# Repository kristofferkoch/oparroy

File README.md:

# oparroy

A read+write, fault-tolerant ring communication protocol for **extremely
cheap** microcontroller nodes, inspired by the WS2812 single-wire
protocol.

Unlike WS2812's write-only daisy chain, oparroy closes the chain into a
ring so nodes can both send and receive. The physical layer is designed
so that **no single point of failure** — a broken connector (permanent
or intermittent), or a dead/hung microcontroller — partitions the ring:

- The ring is dual: every segment carries two counter-rotating data
  rings with symmetric rebroadcast, so any single fault leaves every
  node reachable ([DESIGN.md §3](DESIGN.md#3-ring-topology-and-bypass)).
- Bypass wiring routes around failed interconnects.
- Each node has a semi-passive hardware watchdog that bypasses the
  node's RX→TX path unless the MCU actively keeps the bypass disabled.
- Status LEDs make faults visually locatable to node and segment
  without instruments.

**Extremely low node cost is the central design principle** (sub-3-NOK
MCU class); every other driver — resilience, repairability,
testability — is achieved subject to it. Supervisor and test
infrastructure, by contrast, may cost freely.

## Hardware direction

- **Node MCU: CH32V003F4P6** — 48 MHz
  RV32EC in TSSOP-20, on-chip comparator routable to timer capture,
  ~$0.14 @4k. Clocked from the factory-trimmed internal HSI — no
  crystal; the ratio-metric PHY makes absolute clock accuracy
  irrelevant. Rationale:
  [docs/mcu-research.md](docs/mcu-research.md);
  extracted part facts: `datasheets/CH32V003/notes/`.
- **Supervisor: RP2040** — its PIO is the re-timing PHY engine and
  golden-reference transceiver; on the test board its PIO also runs as
  a logic analyzer on the instrumented boundary node ([DESIGN.md §6](DESIGN.md#6-test-board)).
- **PHY**: WS2812-compatible duty-coded
  PWM cells with ratio-metric decode at an 800 kbit/s anchor,
  comparator RX + DMA, per-bit cut-through re-timing, positional
  addressing, and the frame gap as a ring-wide vsync latch
  ([DESIGN.md §2](DESIGN.md#2-physical-layer); analysis:
  [docs/phy-analysis.md](docs/phy-analysis.md)).
- **Segment interconnect** ([DESIGN.md §2.1](DESIGN.md#21-ring-power-rail), [§3](DESIGN.md#3-ring-topology-and-bypass)): 2x5-pin IDC
  connectors (2.54 mm box headers on 3M 3365/10 ribbon) carry both
  counter-rotating data rings plus power — a single 3.3 V
  rail that is both the signaling rail and node power, and a raw
  5–18 V rail for payloads with their own buck. On 3M 3365 ribbon,
  segments reach **10 m unamplified**; the 470 Ω TX series resistor,
  not the cable, sets the limit (simulation:
  [docs/cable-reach.md](docs/cable-reach.md)).
- **Node I/O**: potmeter, buttons/matrix, capacitive touch, I2C
  accelerometer, LEDs, buzzer — nodes are smart peripherals serving
  cooked data (Bela/Trill pattern, see
  [docs/bela-lessons.md](docs/bela-lessons.md)).
- **Test board**: 8 ring nodes + supervisor, full fault injection
  (per-segment open/short, per-node power cut, keep-alive cut), everything
  scriptable for hands-off hardware-in-the-loop testing. Doubles as
  the **demonstrator**: some nodes carry human-facing I/O
  (potentiometer, buttons, LEDs, buzzer), each input overridable by
  the supervisor so scripted runs stay hands-off ([DESIGN.md §6](DESIGN.md#6-test-board)).
  4-layer, self-documenting silkscreen. Prototypes assembled by
  **JLCPCB Economic PCBA**; part
  selection is inventory-driven — minimize unique Extended BOM lines.

## Firmware direction

- **Freestanding C++, no standard library** — RAII, typed volatile
  structs over memory-mapped I/O, `constexpr` config; no
  exceptions/RTTI/heap.
- Foundation library modeled on **SerenityOS's AK**, landed in
  `firmware/lib/`: `ErrorOr<T>` with `TRY` propagation and fallible
  `try_*` APIs, `VERIFY` with a target failure hook, fixed-capacity
  `StaticVector`/`Span`, and a `StaticArena` slot pool.
- **Ring protocol core** in `firmware/protocol/` — bit cells and
  node/ring forwarding logic ([DESIGN.md §2](DESIGN.md#2-physical-layer)) — proven by **KLEE**
  symbolic-execution harnesses and **libFuzzer** harnesses whose seed
  corpora double as the meson test suite; branch coverage is measured
  on the release build (`scripts/coverage-release`).
- The node pin map is captured in the DSL — 17 of 18 CH32V003 GPIO
  assigned with a budget check — and emits `firmware/node/pins.hpp`
  directly ([DESIGN.md §7](DESIGN.md#7-design-capture-dsl)).
- All of it under the project-owned coding standard:
  [code-std.md](code-std.md) holds the language-independent rules and
  links the per-language standards
  ([code-std-cpp.md](code-std-cpp.md),
  [code-std-python.md](code-std-python.md)) — borrowing from
  JSF AV / MISRA / AUTOSAR / CERT, statically checked
  from the first commit ([DESIGN.md §8](DESIGN.md#8-verification-strategy)).

## Tooling

- **Design capture is code**: the home-rolled Python DSL
  (`src/oparroy/dsl/`, [DESIGN.md §7](DESIGN.md#7-design-capture-dsl)) is the single source of truth —
  an IR with subcircuit composition (ports, port arrays, bundles,
  multipacking, component sockets), a validation pass (limit ranges,
  interval containment, waivers as data), and emitters for KiCad
  netlists, ngspice simulation netlists, and firmware pin headers.
  Footprint assignment and annotation/back-annotation are explicit,
  repeatable stages between capture and pcbnew, so emission is not a
  one-shot export. The parts DB carries assembler-stock status
  (inventory-driven selection), and a `.kicad_pcb` layout property
  checker audits the physical layout (stackup, trace budgets,
  bypass-path copper independence, mechanical contracts). KiCad is
  used for layout only. Learn the DSL from
  [docs/dsl-tutorial.md](docs/dsl-tutorial.md); the API map is
  [docs/dsl-reference.md](docs/dsl-reference.md). Circuit captures live
  in `design/` — the full
  node board is captured (CH32V003 + PHY front-end + charge-pump
  watchdog + status LEDs + segment connectors) — with ngspice benches
  in `circuits/` run via `scripts/sim-run`.
- **Datasheets are extracted, not just stored**: `datasheets/<PART>/`
  holds vendor PDFs plus LLM-readable markdown sidecars (facts,
  per-peripheral notes, quirks) — see `datasheets/README.md`.
- **Meson + ninja** build the firmware ([DESIGN.md §8](DESIGN.md#8-verification-strategy)): one build
  dir per toolchain, freestanding flag set in `meson.build`.
  - host (clang; host objects + LLVM bitcode for KLEE):
    `meson setup build/host --native-file meson/native/clang.ini`
  - CH32V003 (RV32EC objects):
    `meson setup build/rv32ec --cross-file meson/cross/rv32ec.ini`
  - then `meson compile -C build/<dir>`; the reproducibility gate
    `ninja -C build/host check-reproducible` builds every
    configuration twice and compares artifact hashes.
- **nix flake** provides everything non-Python (riscv/arm cross GCC,
  clang 19 + KLEE, AFL++, ngspice, KiCad, uv itself), pinned by
  `flake.lock` — `nix develop` enters the shell (`.envrc` provided for
  direnv users); **uv** owns Python alone (3.14, ruff strict, ty,
  pytest): `uv sync`, then `uv run pytest` / `uv run ruff check` /
  `uv run ty check`.
- **Pre-commit hooks** (`pre-commit install`): clang-format,
  clang-tidy (replaying the host build's `compile_commands.json`), and
  the markdown pipeline
  (mdformat + markdownlint-cli2 + lychee link checks) — cheap checks
  only, ~2 s warm. Hooks are `language: system` against the
  nix-pinned tools, so the flake stays the single tool source.
- **CI** (`.github/workflows/ci.yml`): GitHub Actions runs every gate
  — pytest, firmware host build + unit tests, KLEE proofs, bounded
  fuzz runs, ngspice benches, the rv32ec cross build, the
  reproducibility gate, and the pre-commit suite — inside the nix dev
  shell, so CI exercises byte-identical tools to a laptop. Each gate
  sparse-checks-out only its declared inputs, so an undeclared
  dependency fails CI even when the full tree builds locally;
  `scripts/check-sparse <gate>` rehearses a gate against a sparse
  worktree before pushing (file content comes from `HEAD` — commit
  source edits first).

## Repository layout

| Path                         | Contents                                                                                                                                                  |
| ---------------------------- | --------------------------------------------------------------------------------------------------------------------------------------------------------- |
| `AGENTS.md`                  | Doc-split and writing conventions for agents                                                                                                              |
| `IDEAS.md`                   | Not-yet-planned ideas (append-only stash)                                                                                                                 |
| `DESIGN.md`                  | Settled design decisions + open design questions                                                                                                          |
| `KANBAN.md`                  | Single home for planned work (cards, Next/Backlog)                                                                                                        |
| `code-std.md`                | Project-owned coding standard: general rules (living)                                                                                                     |
| `code-std-cpp.md`            | C++ coding standard (living)                                                                                                                              |
| `code-std-python.md`         | Python (DSL) coding standard (living)                                                                                                                     |
| `README.md`                  | This file                                                                                                                                                 |
| `flake.nix` + `flake.lock`   | Pinned dev shell: all non-Python tools ([DESIGN.md §8](DESIGN.md#8-verification-strategy))                                                                |
| `pyproject.toml` + `uv.lock` | Python side: the DSL package (ruff strict, ty, pytest)                                                                                                    |
| `src/oparroy/`               | Design-capture DSL package (`dsl/`: IR, checks, emitters)                                                                                                 |
| `design/`                    | DSL circuit captures: node board, pin map, parts DB seed                                                                                                  |
| `circuits/`                  | ngspice benches: PHY segment, watchdog, cable reach                                                                                                       |
| `tests/`                     | Python tests (pytest) + golden netlists, `.kicad_pcb` fixtures                                                                                            |
| `meson.build` + `meson/`     | Firmware build: flag set, native/cross toolchain files                                                                                                    |
| `.envrc`                     | direnv hook into the flake shell                                                                                                                          |
| `.pre-commit-config.yaml`    | Hook wiring; tools nix-pinned, `language: system`                                                                                                         |
| `.github/workflows/`         | CI: every gate inside the nix shell                                                                                                                       |
| `firmware/`                  | Node/supervisor firmware: foundation lib, ring protocol                                                                                                   |
| `scripts/`                   | Build, sim/proof/fuzz, coverage + pre-commit scripts (sh)                                                                                                 |
| `docs/`                      | Reference documents (research reports, sub-designs); [dsl-tutorial.md](docs/dsl-tutorial.md) + [dsl-reference.md](docs/dsl-reference.md) document the DSL |
| `datasheets/`                | Vendor PDFs + extracted markdown sidecars per part                                                                                                        |
| `LICENSE`                    | MIT, copyright 2026 Kristoffer Koch                                                                                                                       |

Doc conventions follow the IDEAS → KANBAN/DESIGN graduation model:
stray thoughts live in IDEAS.md, planned work in KANBAN.md cards,
settled decisions in DESIGN.md. See
[AGENTS.md §Documentation](AGENTS.md#documentation--the-ideas--kanban--design-split).

## Status

The design-automation pipeline is landed end-to-end: the DSL captures
the full node board, validates it, and emits KiCad and ngspice
netlists, the firmware pin header, and layout constraint skeletons;
simulation benches cover the PHY, the charge-pump watchdog, and cable
reach. On the firmware side the foundation library and the
ring-protocol core are in place under KLEE/fuzz/coverage verification,
and CI runs every gate. No boards exist yet: next up is KiCad layout
of the node board, which unblocks the 8-node test board and the
long-cable bench work. Current work is tracked as cards
in `KANBAN.md`.

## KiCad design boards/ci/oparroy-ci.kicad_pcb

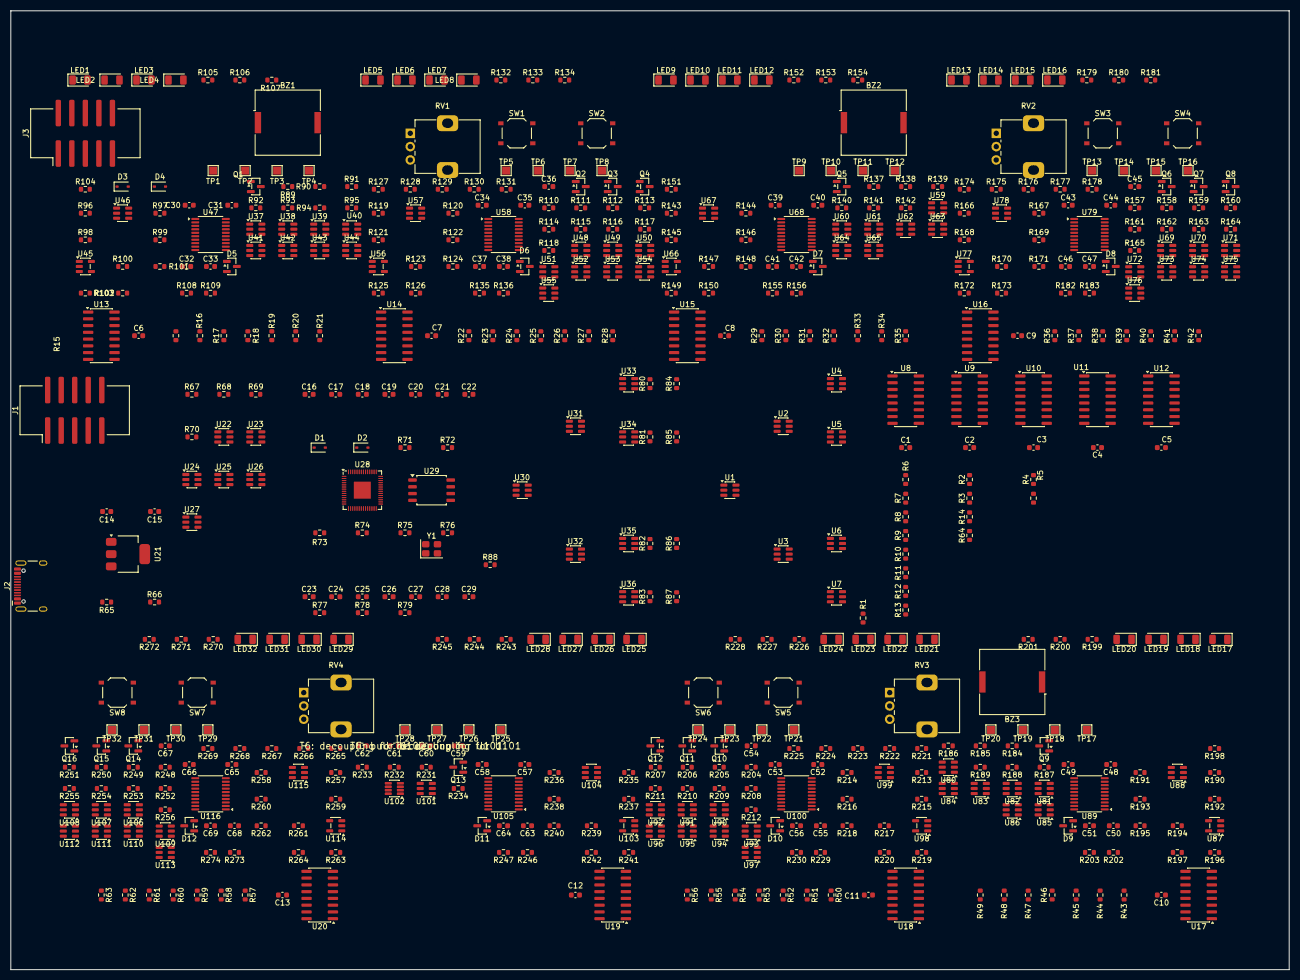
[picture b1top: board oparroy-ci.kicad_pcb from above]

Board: 4 copper layers, 240.0 x 180.0 mm, 570 parts (0 on the bottom side), 426 nets, no tracks yet.

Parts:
BZ1, BZ2, BZ3: PKLCS1212E4001-R1; Buzzer_Murata_PKLCS1212E
C1, C2, C3, C4, C5, C6, C7, C8, C9, C10, C11, C12, C13, C18, C19, C20, C21, C22, C23, C24, C25, C26, C27, C30, C34, C36, C39, C43, C45, C48, C52, C54, C57, C59, C62, C65, C67: 100n; C_0603_1608Metric
C14, C31, C35, C40, C44, C49, C53, C58, C66: 10u; C_0603_1608Metric
C15: 22u; C_0603_1608Metric
C16, C17: 15p; C_0603_1608Metric
C28, C29, C60: 1u; C_0603_1608Metric
C32, C37, C41, C46, C50, C55, C63, C68: 22n; C_0603_1608Metric
C33, C38, C42, C47, C51, C56, C64, C69: 10n; C_0603_1608Metric
C61: 1n; C_0603_1608Metric
D1, D2, D3, D4: UDD32C03L01; D_SOD-323
D5, D6, D7, D8, D9, D10, D11, D12: BAT54S; SOT-23
J1, J3: Conn_02x05_Odd_Even; IDC-Header_2x05_P2.54mm_Vertical_SMD
J2: HC-TYPE-C-16P-01A; USB_C_Receptacle_HCTL_HC-TYPE-C-16P-01A
LED1, LED3, LED5, LED7, LED9, LED11, LED13, LED15, LED17, LED19, LED21, LED23, LED25, LED27, LED29, LED31: XL-3216SYGC; LED_1206_3216Metric
LED2, LED6, LED10, LED14, LED18, LED22, LED26, LED30: XL-3216SURC; LED_1206_3216Metric
LED4, LED8, LED12, LED16, LED20, LED24, LED28, LED32: XL-3216UYC; LED_1206_3216Metric
Q1, Q4, Q5, Q8, Q9, Q12, Q13, Q16: AO3401A; SOT-23
Q2, Q3, Q6, Q7, Q10, Q11, Q14, Q15: 2N7002; SOT-23
R1, R2, R3, R4, R5, R6, R7, R8, R9, R10, R11, R12, R13, R14, R15, R16, R17, R18, R19, R20, R21, R22, R23, R24, R25, R26, R27, R28, R29, R30, R31, R32, R33, R34, R35, R36, R37, R38, R39, R40, R41, R42, R43, R44, R45, R46, R47, R48, R49, R50, R51, R52, R53, R54, R55, R56, R57, R58, R59, R60, R61, R62, R63, R64, R93, R94, R108, R112, R113, R116, R118, R135, R141, R142, R155, R159, R160, R163, R165, R182, R188, R189, R202, R206, R207, R210, R212, R229, R231, R233, R246, R250, R251, R254, R256, R273: 47k; R_0603_1608Metric
R65, R66: 5k1; R_0603_1608Metric
R67, R68, R69, R70, R76, R77, R78, R79, R89, R90, R91, R92, R95, R96, R97, R98, R99, R104, R106, R110, R111, R114, R115, R119, R120, R121, R122, R133, R137, R138, R139, R140, R143, R144, R145, R146, R151, R153, R157, R158, R161, R162, R166, R167, R168, R169, R180, R184, R185, R186, R187, R190, R191, R192, R193, R198, R200, R204, R205, R208, R209, R213, R214, R215, R216, R227, R235, R236, R237, R238, R244, R248, R249, R252, R253, R257, R258, R259, R260, R271: 470; R_0603_1608Metric
R71, R73, R105, R107, R129, R130, R131, R132, R134, R152, R154, R176, R177, R178, R179, R181, R199, R201, R223, R224, R225, R226, R228, R243, R245, R267, R268, R269, R270, R272: 1k; R_0603_1608Metric
R72, R80, R81, R82, R83, R84, R85, R86, R87, R102, R103, R117, R125, R126, R127, R128, R149, R150, R164, R172, R173, R174, R175, R196, R197, R211, R219, R220, R221, R222, R241, R242, R255, R263, R264, R265, R266: 10k; R_0603_1608Metric
R74, R75: 27; R_0603_1608Metric
R88: 4k7; R_0603_1608Metric
R100, R123, R147, R170, R194, R217, R239, R261: DNP; R_0603_1608Metric
R101, R124, R148, R171, R195, R218, R240, R262: 0R; R_0603_1608Metric
R109, R136, R156, R183, R203, R230, R247, R274: 220; R_0603_1608Metric
R232: 47; R_0603_1608Metric
R234: R082; R_0603_1608Metric
RV1, RV2, RV3, RV4: 10k; Potentiometer_Alps_RK09K_Single_Vertical
SW1, SW2, SW3, SW4, SW5, SW6, SW7, SW8: TS-1187A-B-A-B; SW_Push_1P1T_XKB_TS-1187A
TP1, TP5, TP9, TP13, TP17, TP21, TP25, TP29: SWIO; TestPoint_Pad_1.5x1.5mm
TP2, TP6, TP10, TP14, TP18, TP22, TP26, TP30: 3V3; TestPoint_Pad_1.5x1.5mm
TP3, TP7, TP11, TP15, TP19, TP23, TP27, TP31: GND; TestPoint_Pad_1.5x1.5mm
TP4, TP8, TP12, TP16, TP20, TP24, TP28, TP32: PC7; TestPoint_Pad_1.5x1.5mm
U1, U2, U3, U4, U5, U6, U7, U30, U31, U32, U33, U34, U35, U36, U46, U57, U67, U78, U88, U99, U104, U115: SN74LVC1G3157; SOT-23-6
U8, U9, U10, U13, U14, U15, U16, U17, U18, U19, U20: 74HC595; SOIC-16_3.9x9.9mm_P1.27mm
U11, U12: 74HC165; SOIC-16_3.9x9.9mm_P1.27mm
U21: AMS1117-3.3; SOT-223-3_TabPin2
U22, U23, U24, U25, U26, U27, U37, U38, U39, U40, U41, U42, U43, U44, U48, U49, U50, U51, U52, U53, U54, U55, U59, U60, U61, U62, U63, U64, U65, U69, U70, U71, U72, U73, U74, U75, U76, U80, U81, U82, U83, U84, U85, U86, U90, U91, U92, U93, U94, U95, U96, U97, U106, U107, U108, U109, U110, U111, U112, U113: 74LVC1G3157; SOT-23-6
U28: RP2040; QFN-56-1EP_7x7mm_P0.4mm_EP3.2x3.2mm
U29: W25Q16JVSSIQ; SOIC-8_5.3x5.3mm_P1.27mm
U45, U56, U66, U77, U87, U98, U103, U114: DNP; SOT-23-5
U47, U58, U68, U79, U89, U100, U105, U116: CH32V003F4P6; TSSOP-20_4.4x6.5mm_P0.65mm
U101: ADCS7476; SOT-23-6
U102: INA241A5; SOT-23-8
Y1: ABM8-272-T3; Crystal_SMD_3225-4Pin_3.2x2.5mm

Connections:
3V3: C1.1, C2.1, C3.1, C4.1, C5.1, C6.1, C7.1, C8.1, C9.1, C10.1, C11.1, C12.1, C13.1, C15.1, C18.1, C21.1, C22.1, C23.1, C24.1, C25.1, C26.1, C27.1, C28.1, C59.1, C60.1, C62.1, J1.3, J1.9, J3.3, J3.9, Q1.2, Q4.2, Q5.2, Q8.2, Q9.2, Q12.2, Q13.2, Q16.2, R1.2, R68.2, R70.2, R72.2, R88.2, R90.2, R92.2, R95.2, R111.2, R115.2, R138.2, R140.2, R158.2, R162.2, R185.2, R187.2, R205.2, R209.2, R231.2, R249.2, R253.2, U1.5, U2.5, U3.5, U4.5, U5.5, U6.5, U7.5, U8.10, U8.16, U9.10, U9.16, U10.10, U10.16, U11.16, U12.16, U13.10, U13.16, U14.10, U14.16, U15.10, U15.16, U16.10, U16.16, U17.10, U17.16, U18.10, U18.16, U19.10, U19.16, U20.10, U20.16, U21.2, U22.5, U23.5, U24.5, U25.5, U26.5, U27.5, U28.1, U28.10, U28.22, U28.26, U28.33, U28.42, U28.43, U28.44, U28.48, U28.49, U29.8, U30.5, U31.5, U32.5, U33.5, U34.5, U35.5, U36.5, U37.5, U38.5, U39.5, U40.5, U41.5, U42.5, U43.5, U44.5, U45.5, U46.5, U48.5, U49.5, U50.5, U51.5, U52.5, U53.5, U54.5, U55.5, U56.5, U57.5, U59.5, U60.5, U61.5, U62.5, U63.5, U64.5, U65.5, U66.5, U67.5, U69.5, U70.5, U71.5, U72.5, U73.5, U74.5, U75.5, U76.5, U77.5, U78.5, U80.5, U81.5, U82.5, U83.5, U84.5, U85.5, U86.5, U87.5, U88.5, U90.5, U91.5, U92.5, U93.5, U94.5, U95.5, U96.5, U97.5, U98.5, U99.5, U101.1, U102.6, U102.7, U103.5, U104.5, U106.5, U107.5, U108.5, U109.5, U110.5, U111.5, U112.5, U113.5, U114.5, U115.5
5V: C14.1, J2.A4, J2.A9, J2.B4, J2.B9, U21.3
CABLE_A: D3.1, J3.5, R96.1
CABLE_B: D4.1, J3.7, R99.2
DBG/low0: U2.3, U4.4
DBG/low1: U2.1, U5.4
DBG/low2: U3.3, U6.4
DBG/low3: U3.1, U7.4
DBG/mid0: U1.3, U2.4
DBG/mid1: U1.1, U3.4
GND: BZ1.2, BZ2.2, BZ3.2, C1.2, C2.2, C3.2, C4.2, C5.2, C6.2, C7.2, C8.2, C9.2, C10.2, C11.2, C12.2, C13.2, C14.2, C15.2, C16.2, C17.2, C18.2, C19.2, C20.2, C21.2, C22.2, C23.2, C24.2, C25.2, C26.2, C27.2, C28.2, C29.2, C30.2, C31.2, C33.2, C34.2, C35.2, C36.2, C38.2, C39.2, C40.2, C42.2, C43.2, C44.2, C45.2, C47.2, C48.2, C49.2, C51.2, C52.2, C53.2, C54.2, C56.2, C57.2, C58.2, C59.2, C60.2, C61.2, C62.2, C64.2, C65.2, C66.2, C67.2, C69.2, D1.2, D2.2, D3.2, D4.2, D5.1, D6.1, D7.1, D8.1, D9.1, D10.1, D11.1, D12.1, J1.2, J1.4, J1.6, J1.8, J1.10, J2.A1, J2.A12, J2.B1, J2.B12, J2.SH, J3.2, J3.4, J3.6, J3.8, J3.10, LED2.1, LED3.1, LED4.1, LED6.1, LED7.1, LED8.1, LED10.1, LED11.1, LED12.1, LED14.1, LED15.1, LED16.1, LED18.1, LED19.1, LED20.1, LED22.1, LED23.1, LED24.1, LED26.1, LED27.1, LED28.1, LED30.1, LED31.1, LED32.1, Q2.2, Q3.2, Q6.2, Q7.2, Q10.2, Q11.2, Q14.2, Q15.2, R2.2, R3.2, R4.2, R5.2, R6.2, R7.2, R8.2, R9.2, R10.2, R11.2, R12.2, R13.2, R14.2, R15.2, R16.2, R17.2, R18.2, R19.2, R20.2, R21.2, R22.2, R23.2, R24.2, R25.2, R26.2, R27.2, R28.2, R29.2, R30.2, R31.2, R32.2, R33.2, R34.2, R35.2, R36.2, R37.2, R38.2, R39.2, R40.2, R41.2, R42.2, R43.2, R44.2, R45.2, R46.2, R47.2, R48.2, R49.2, R50.2, R51.2, R52.2, R53.2, R54.2, R55.2, R56.2, R57.2, R58.2, R59.2, R60.2, R61.2, R62.2, R63.2, R64.2, R65.2, R66.2, R67.2, R69.2, R89.2, R91.2, R93.2, R94.2, R103.2, R108.2, R110.2, R112.2, R113.2, R114.2, R116.2, R118.2, R126.2, R135.2, R137.2, R139.2, R141.2, R142.2, R150.2, R155.2, R157.2, R159.2, R160.2, R161.2, R163.2, R165.2, R173.2, R182.2, R184.2, R186.2, R188.2, R189.2, R197.2, R202.2, R204.2, R206.2, R207.2, R208.2, R210.2, R212.2, R220.2, R229.2, R233.2, R242.2, R246.2, R248.2, R250.2, R251.2, R252.2, R254.2, R256.2, R264.2, R273.2, RV1.3, RV2.3, RV3.3, RV4.3, SW1.2, SW2.2, SW3.2, SW4.2, SW5.2, SW6.2, SW7.2, SW8.2, TP3.1, TP7.1, TP11.1, TP15.1, TP19.1, TP23.1, TP27.1, TP31.1, U1.2, U2.2, U3.2, U4.2, U5.2, U6.2, U7.2, U8.8, U9.8, U10.8, U11.8, U11.15, U12.8, U12.15, U13.8, U14.8, U15.8, U16.8, U17.8, U18.8, U19.8, U20.8, U21.1, U22.2, U23.2, U24.2, U25.2, U26.2, U27.2, U28.19, U28.57, U29.4, U30.2, U31.2, U32.2, U33.2, U34.2, U35.2, U36.2, U37.2, U38.2, U39.2, U40.2, U41.2, U42.2, U43.2, U44.2, U45.3, U46.2, U47.7, U48.2, U49.2, U50.2, U51.2, U52.2, U53.2, U54.2, U55.2, U56.3, U57.2, U58.7, U59.2, U60.2, U61.2, U62.2, U63.2, U64.2, U65.2, U66.3, U67.2, U68.7, U69.2, U70.2, U71.2, U72.2, U73.2, U74.2, U75.2, U76.2, U77.3, U78.2, U79.7, U80.2, U81.2, U82.2, U83.2, U84.2, U85.2, U86.2, U87.3, U88.2, U89.7, U90.2, U91.2, U92.2, U93.2, U94.2, U95.2, U96.2, U97.2, U98.3, U99.2, U100.7, U101.2, U102.2, U102.3, U102.4, U103.3, U104.2, U105.7, U106.2, U107.2, U108.2, U109.2, U110.2, U111.2, U112.2, U113.2, U114.3, U115.2, U116.7, Y1.2, Y1.4
PLANE/chain_aux0: U8.9, U9.14
PLANE/chain_aux1: U9.9, U10.14
PLANE/chain_aux2: U10.9, U13.14
PLANE/chain_obs0: U11.9, U12.10
PLANE/chain_t0: U13.9, U14.14
PLANE/chain_t1: U14.9, U15.14
PLANE/chain_t2: U15.9, U16.14
PLANE/chain_t3: U16.9, U17.14
PLANE/chain_t4: U17.9, U18.14
PLANE/chain_t5: U18.9, U19.14
PLANE/chain_t6: U19.9, U20.14
PLANE/chain_t7: U11.10, U20.9
PWR/cc1: J2.A5, R65.1
PWR/cc2: J2.B5, R66.1
SEG0_A: D1.1, J1.5, U22.3, U23.4, U24.4
SEG0_B: D2.1, J1.7, U25.3, U26.4, U27.4
SEG1_A: R119.1, U28.12, U37.3, U38.4, U39.4
SEG1_B: R122.2, U40.3, U41.4, U42.4
SEG2_A: R143.1, U48.3, U49.4, U50.4
SEG2_B: R146.2, U51.3, U52.4, U53.4
SEG3_A: R166.1, U59.3, U60.4, U61.4
SEG3_B: R169.2, U62.3, U63.4, U64.4
SEG4_A: R190.1, U69.3, U70.4, U71.4
SEG4_B: R193.2, U72.3, U73.4, U74.4
SEG5_A: R213.1, U80.3, U81.4, U82.4
SEG5_B: R216.2, U83.3, U84.4, U85.4
SEG6_A: R235.1, U90.3, U91.4, U92.4
SEG6_B: R238.2, U93.3, U94.4, U95.4
SEG7_A: R236.2, R257.1
SEG7_B: R237.1, R260.2
SEG8_A: R76.1, U106.3, U107.4, U108.4
SEG8_B: R79.2, U109.3, U110.4, U111.4
SUP/BRK_A: R6.1, U8.15, U22.6
SUP/BRK_B: R7.1, U8.3, U25.6
SUP/F2_leg: R67.1, U23.1
SUP/F3_leg: R68.1, U24.1
SUP/F5_leg: R69.1, U26.1
SUP/F6_leg: R70.1, U27.1
SUP/RX_B#a: R78.1, U25.4
SUP/SHG_A: R8.1, U8.1, U23.6
SUP/SHG_B: R9.1, U8.4, U26.6
SUP/SHV_A: R10.1, U8.2, U24.6
SUP/SHV_B: R11.1, U8.5, U27.6
SUP/TX_A#a: R77.2, U22.4
SUP/dvdd: C19.1, C20.1, C29.1, U28.23, U28.45, U28.50
SUP/qspi_sclk: U28.52, U29.6
SUP/qspi_sd0: U28.53, U29.5
SUP/qspi_sd1: U28.55, U29.2
SUP/qspi_sd2: U28.54, U29.3
SUP/qspi_sd3: U28.51, U29.7
SUP/qspi_ss: R71.1, R72.1, U28.56, U29.1
SUP/ring_rxa: R76.2, U28.8
SUP/ring_rxb: R78.2, U28.7
SUP/ring_txa: R77.1, U28.6
SUP/ring_txb: R79.1, U28.9
SUP/usb_dm_r: R75.2, U28.46
SUP/usb_dp_r: R74.2, U28.47
SUP/xin: C16.1, U28.20, Y1.1
SUP/xosc: C17.1, R73.2, Y1.3
SUP/xout: R73.1, U28.21
SWIO/low0: U31.3, U33.4
SWIO/low1: U31.1, U34.4
SWIO/low2: U32.3, U35.4
SWIO/low3: U32.1, U36.4
SWIO/mid0: U30.3, U31.4
SWIO/mid1: U30.1, U32.4
T0/3V3N: C30.1, C31.1, LED1.2, Q1.3, R80.2, R102.1, R105.1, TP2.1, U11.12, U47.9
T0/B5_leg: R95.1, U44.1
T0/BRK_A: R15.1, U13.15, U37.6
T0/BRK_B: R16.1, U13.3, U40.6
T0/F2_leg: R89.1, U38.1
T0/F3_leg: R90.1, U39.1
T0/F5_leg: R91.1, U41.1
T0/F6_leg: R92.1, U42.1
T0/KA_CUT: R17.1, U13.6, U43.6
T0/PHY1/sel_sw: R101.2, U45.4, U46.6
T0/PHY1/txa_sw: R97.1, U46.4
T0/PWR: Q1.1, R94.1, U13.7
T0/RX_B#a: R98.1, U40.4
T0/SHG_A: R18.1, U13.1, U38.6
T0/SHG_B: R19.1, U13.4, U41.6
T0/SHV_A: R20.1, U13.2, U39.6
T0/SHV_B: R21.1, U13.5, U42.6
T0/SL1/led_x: LED1.1, LED3.2, R106.2
T0/SL1/ledw_a: LED4.2, R107.2
T0/SL1/pwr_led: LED2.2, R105.2
T0/TX_A#a: R97.2, U37.4
T0/WD1/kap: C32.1, R109.2
T0/WD1/x: C32.2, D5.3
T0/WD_DEFEAT: R64.1, U9.1, U44.6
T0/buzzer: R104.1, U47.14
T0/bz: BZ1.1, R104.2
T0/debug_tx: U4.3, U47.2
T0/ka#a: U43.4, U47.20
T0/ka#b: R93.1, R109.1, U43.3
T0/led_seg: R106.1, U47.10
T0/led_work: R107.1, U28.14, U47.8
T0/opa_n: R102.2, R103.1, U47.5
T0/opa_p: R96.2, R100.2, U28.11, U46.3, U47.6
T0/opa_p_b: R98.2, U47.4
T0/opo: R100.1, U28.13, U47.1
T0/pc7: TP4.1, U47.17
T0/sel: C33.1, D5.2, R101.1, R108.1, U11.11, U44.4, U45.2, U47.12
T0/swio: R80.1, TP1.1, U33.3, U47.18
T0/txa_drv: U46.1, U47.19
T0/txb_drv: R99.1, U47.13
T1/3V3N: C34.1, C35.1, LED5.2, Q4.3, R81.2, R125.1, R127.2, R128.2, R132.1, RV1.1, TP6.1, U11.14, U58.9
T1/BRK_A: R22.1, U14.15, U48.6
T1/BRK_B: R23.1, U14.3, U51.6
T1/BTN_A: Q2.1, R112.1, U9.3
T1/BTN_B: Q3.1, R113.1, U9.4
T1/F2_leg: R110.1, U49.1
T1/F3_leg: R111.1, U50.1
T1/F5_leg: R114.1, U52.1
T1/F6_leg: R115.1, U53.1
T1/H1_filt: C36.1, R117.2, U55.1
T1/KA_CUT: R24.1, U14.6, U54.6
T1/PHY1/sel_sw: R124.2, U56.4, U57.6
T1/PHY1/txa_sw: R120.1, U57.4
T1/POT_PWM: R117.1, U28.17
T1/POT_SEL: R2.1, U9.2, U55.6
T1/PWR: Q4.1, R118.1, U14.7
T1/RX_B#a: R121.1, U51.4
T1/SHG_A: R25.1, U14.1, U49.6
T1/SHG_B: R26.1, U14.4, U52.6
T1/SHV_A: R27.1, U14.2, U50.6
T1/SHV_B: R28.1, U14.5, U53.6
T1/SL1/led_x: LED5.1, LED7.2, R133.2
T1/SL1/ledw_a: LED8.2, R134.2
T1/SL1/pwr_led: LED6.2, R132.2
T1/TX_A#a: R120.2, U48.4
T1/WD1/kap: C37.1, R136.2
T1/WD1/x: C37.2, D6.3
T1/btn_a: Q2.3, R127.1, R129.1, SW1.1
T1/btn_b: Q3.3, R128.1, R130.1, SW2.1
T1/button_a: R129.2, U58.15
T1/button_b: R130.2, U58.16
T1/debug_tx: U4.1, U58.2
T1/ka#a: U54.4, U58.20
T1/ka#b: R116.1, R136.1, U54.3
T1/led_seg: R133.1, U58.10
T1/led_work: R134.1, U58.8
T1/opa_n: R125.2, R126.1, U58.5
T1/opa_p: R119.2, R123.2, U57.3, U58.6
T1/opa_p_b: R121.2, U58.4
T1/opo: R123.1, U58.1
T1/pc7: TP8.1, U58.17
T1/pot: R131.2, U58.3
T1/pot_w#a: RV1.2, U55.3
T1/pot_w#b: R131.1, U55.4
T1/sel: C38.1, D6.2, R124.1, R135.1, U11.13, U56.2, U58.12
T1/swio: R81.1, TP5.1, U33.1, U58.18
T1/txa_drv: U57.1, U58.19
T1/txb_drv: R122.1, U58.13
T2/3V3N: C39.1, C40.1, LED9.2, Q5.3, R82.2, R149.1, R152.1, TP10.1, U11.4, U68.9
T2/BRK_A: R29.1, U15.15, U59.6
T2/BRK_B: R30.1, U15.3, U62.6
T2/F2_leg: R137.1, U60.1
T2/F3_leg: R138.1, U61.1
T2/F5_leg: R139.1, U63.1
T2/F6_leg: R140.1, U64.1
T2/KA_CUT: R31.1, U15.6, U65.6
T2/PHY1/sel_sw: R148.2, U66.4, U67.6
T2/PHY1/txa_sw: R144.1, U67.4
T2/PWR: Q5.1, R142.1, U15.7
T2/RX_B#a: R145.1, U62.4
T2/SHG_A: R32.1, U15.1, U60.6
T2/SHG_B: R33.1, U15.4, U63.6
T2/SHV_A: R34.1, U15.2, U61.6
T2/SHV_B: R35.1, U15.5, U64.6
T2/SL1/led_x: LED9.1, LED11.2, R153.2
T2/SL1/ledw_a: LED12.2, R154.2
T2/SL1/pwr_led: LED10.2, R152.2
T2/TX_A#a: R144.2, U59.4
T2/WD1/kap: C41.1, R156.2
T2/WD1/x: C41.2, D7.3
T2/buzzer: R151.1, U68.14
T2/bz: BZ2.1, R151.2
T2/debug_tx: U5.3, U68.2
T2/ka#a: U65.4, U68.20
T2/ka#b: R141.1, R156.1, U65.3
T2/led_seg: R153.1, U68.10
T2/led_work: R154.1, U68.8
T2/opa_n: R149.2, R150.1, U68.5
T2/opa_p: R143.2, R147.2, U67.3, U68.6
T2/opa_p_b: R145.2, U68.4
T2/opo: R147.1, U68.1
T2/pc7: TP12.1, U68.17
T2/sel: C42.1, D7.2, R148.1, R155.1, U11.3, U66.2, U68.12
T2/swio: R82.1, TP9.1, U34.3, U68.18
T2/txa_drv: U67.1, U68.19
T2/txb_drv: R146.1, U68.13
T3/3V3N: C43.1, C44.1, LED13.2, Q8.3, R83.2, R172.1, R174.2, R175.2, R179.1, RV2.1, TP14.1, U11.6, U79.9
T3/BRK_A: R36.1, U16.15, U69.6
T3/BRK_B: R37.1, U16.3, U72.6
T3/BTN_A: Q6.1, R159.1, U9.6
T3/BTN_B: Q7.1, R160.1, U9.7
T3/F2_leg: R157.1, U70.1
T3/F3_leg: R158.1, U71.1
T3/F5_leg: R161.1, U73.1
T3/F6_leg: R162.1, U74.1
T3/H1_filt: C45.1, R164.2, U76.1
T3/KA_CUT: R38.1, U16.6, U75.6
T3/PHY1/sel_sw: R171.2, U77.4, U78.6
T3/PHY1/txa_sw: R167.1, U78.4
T3/POT_PWM: R164.1, U28.18
T3/POT_SEL: R3.1, U9.5, U76.6
T3/PWR: Q8.1, R165.1, U16.7
T3/RX_B#a: R168.1, U72.4
T3/SHG_A: R39.1, U16.1, U70.6
T3/SHG_B: R40.1, U16.4, U73.6
T3/SHV_A: R41.1, U16.2, U71.6
T3/SHV_B: R42.1, U16.5, U74.6
T3/SL1/led_x: LED13.1, LED15.2, R180.2
T3/SL1/ledw_a: LED16.2, R181.2
T3/SL1/pwr_led: LED14.2, R179.2
T3/TX_A#a: R167.2, U69.4
T3/WD1/kap: C46.1, R183.2
T3/WD1/x: C46.2, D8.3
T3/btn_a: Q6.3, R174.1, R176.1, SW3.1
T3/btn_b: Q7.3, R175.1, R177.1, SW4.1
T3/button_a: R176.2, U79.15
T3/button_b: R177.2, U79.16
T3/debug_tx: U5.1, U79.2
T3/ka#a: U75.4, U79.20
T3/ka#b: R163.1, R183.1, U75.3
T3/led_seg: R180.1, U79.10
T3/led_work: R181.1, U79.8
T3/opa_n: R172.2, R173.1, U79.5
T3/opa_p: R166.2, R170.2, U78.3, U79.6
T3/opa_p_b: R168.2, U79.4
T3/opo: R170.1, U79.1
T3/pc7: TP16.1, U79.17
T3/pot: R178.2, U79.3
T3/pot_w#a: RV2.2, U76.3
T3/pot_w#b: R178.1, U76.4
T3/sel: C47.1, D8.2, R171.1, R182.1, U11.5, U77.2, U79.12
T3/swio: R83.1, TP13.1, U34.1, U79.18
T3/txa_drv: U78.1, U79.19
T3/txb_drv: R169.1, U79.13
T4/3V3N: C48.1, C49.1, LED17.2, Q9.3, R84.2, R196.1, R199.1, TP18.1, U12.12, U89.9
T4/BRK_A: R43.1, U17.15, U80.6
T4/BRK_B: R44.1, U17.3, U83.6
T4/F2_leg: R184.1, U81.1
T4/F3_leg: R185.1, U82.1
T4/F5_leg: R186.1, U84.1
T4/F6_leg: R187.1, U85.1
T4/KA_CUT: R45.1, U17.6, U86.6
T4/PHY1/sel_sw: R195.2, U87.4, U88.6
T4/PHY1/txa_sw: R191.1, U88.4
T4/PWR: Q9.1, R189.1, U17.7
T4/RX_B#a: R192.1, U83.4
T4/SHG_A: R46.1, U17.1, U81.6
T4/SHG_B: R47.1, U17.4, U84.6
T4/SHV_A: R48.1, U17.2, U82.6
T4/SHV_B: R49.1, U17.5, U85.6
T4/SL1/led_x: LED17.1, LED19.2, R200.2
T4/SL1/ledw_a: LED20.2, R201.2
T4/SL1/pwr_led: LED18.2, R199.2
T4/TX_A#a: R191.2, U80.4
T4/WD1/kap: C50.1, R203.2
T4/WD1/x: C50.2, D9.3
T4/buzzer: R198.1, U89.14
T4/bz: BZ3.1, R198.2
T4/debug_tx: U6.3, U89.2
T4/ka#a: U86.4, U89.20
T4/ka#b: R188.1, R203.1, U86.3
T4/led_seg: R200.1, U89.10
T4/led_work: R201.1, U89.8
T4/opa_n: R196.2, R197.1, U89.5
T4/opa_p: R190.2, R194.2, U88.3, U89.6
T4/opa_p_b: R192.2, U89.4
T4/opo: R194.1, U89.1
T4/pc7: TP20.1, U89.17
T4/sel: C51.1, D9.2, R195.1, R202.1, U12.11, U87.2, U89.12
T4/swio: R84.1, TP17.1, U35.3, U89.18
T4/txa_drv: U88.1, U89.19
T4/txb_drv: R193.1, U89.13
T5/3V3N: C52.1, C53.1, LED21.2, Q12.3, R85.2, R219.1, R221.2, R222.2, R226.1, RV3.1, TP22.1, U12.14, U100.9
T5/BRK_A: R50.1, U18.15, U90.6
T5/BRK_B: R51.1, U18.3, U93.6
T5/BTN_A: Q10.1, R206.1, U10.1
T5/BTN_B: Q11.1, R207.1, U10.2
T5/F2_leg: R204.1, U91.1
T5/F3_leg: R205.1, U92.1
T5/F5_leg: R208.1, U94.1
T5/F6_leg: R209.1, U95.1
T5/H1_filt: C54.1, R211.2, U97.1
T5/KA_CUT: R52.1, U18.6, U96.6
T5/PHY1/sel_sw: R218.2, U98.4, U99.6
T5/PHY1/txa_sw: R214.1, U99.4
T5/POT_PWM: R211.1, U28.27
T5/POT_SEL: R4.1, U10.15, U97.6
T5/PWR: Q12.1, R212.1, U18.7
T5/RX_B#a: R215.1, U93.4
T5/SHG_A: R53.1, U18.1, U91.6
T5/SHG_B: R54.1, U18.4, U94.6
T5/SHV_A: R55.1, U18.2, U92.6
T5/SHV_B: R56.1, U18.5, U95.6
T5/SL1/led_x: LED21.1, LED23.2, R227.2
T5/SL1/ledw_a: LED24.2, R228.2
T5/SL1/pwr_led: LED22.2, R226.2
T5/TX_A#a: R214.2, U90.4
T5/WD1/kap: C55.1, R230.2
T5/WD1/x: C55.2, D10.3
T5/btn_a: Q10.3, R221.1, R223.1, SW5.1
T5/btn_b: Q11.3, R222.1, R224.1, SW6.1
T5/button_a: R223.2, U100.15
T5/button_b: R224.2, U100.16
T5/debug_tx: U6.1, U100.2
T5/ka#a: U96.4, U100.20
T5/ka#b: R210.1, R230.1, U96.3
T5/led_seg: R227.1, U100.10
T5/led_work: R228.1, U100.8
T5/opa_n: R219.2, R220.1, U100.5
T5/opa_p: R213.2, R217.2, U99.3, U100.6
T5/opa_p_b: R215.2, U100.4
T5/opo: R217.1, U100.1
T5/pc7: TP24.1, U100.17
T5/pot: R225.2, U100.3
T5/pot_w#a: RV3.2, U97.3
T5/pot_w#b: R225.1, U97.4
T5/sel: C56.1, D10.2, R218.1, R229.1, U12.13, U98.2, U100.12
T5/swio: R85.1, TP21.1, U35.1, U100.18
T5/txa_drv: U99.1, U100.19
T5/txb_drv: R216.1, U100.13
T6/3V3N: C57.1, C58.1, LED25.2, R86.2, R234.2, R241.1, R243.1, TP26.1, U12.4, U102.1, U105.9
T6/F8_adc_in: C61.1, R232.2, U101.3
T6/F8_cs: R231.1, U28.3, U101.6
T6/F8_imeas: R232.1, U102.5
T6/F8_sclk: U28.4, U101.4
T6/F8_sdata: U28.2, U101.5
T6/F8_sns: Q13.3, R234.1, U102.8
T6/PHY1/sel_sw: R240.2, U103.4, U104.6
T6/PHY1/txa_sw: R236.1, U104.4
T6/PWR: Q13.1, R233.1, U19.15
T6/SL1/led_x: LED25.1, LED27.2, R244.2
T6/SL1/ledw_a: LED28.2, R245.2
T6/SL1/pwr_led: LED26.2, R243.2
T6/WD1/kap: C63.1, R247.2
T6/WD1/x: C63.2, D11.3
T6/debug_tx: U7.3, U105.2
T6/ka: R247.1, U105.20
T6/led_seg: R244.1, U105.10
T6/led_work: R245.1, U105.8
T6/opa_n: R241.2, R242.1, U105.5
T6/opa_p: R235.2, R239.2, U104.3, U105.6
T6/opa_p_b: R237.2, U105.4
T6/opo: R239.1, U105.1
T6/pc7: TP28.1, U105.17
T6/sel: C64.1, D11.2, R240.1, R246.1, U12.3, U103.2, U105.12
T6/swio: R86.1, TP25.1, U36.3, U105.18
T6/txa_drv: U104.1, U105.19
T6/txb_drv: R238.1, U105.13
T7/3V3N: C65.1, C66.1, LED29.2, Q16.3, R87.2, R263.1, R265.2, R266.2, R270.1, RV4.1, TP30.1, U12.6, U116.9
T7/BRK_A: R57.1, U20.15, U106.6
T7/BRK_B: R58.1, U20.3, U109.6
T7/BTN_A: Q14.1, R250.1, U10.4
T7/BTN_B: Q15.1, R251.1, U10.5
T7/F2_leg: R248.1, U107.1
T7/F3_leg: R249.1, U108.1
T7/F5_leg: R252.1, U110.1
T7/F6_leg: R253.1, U111.1
T7/H1_filt: C67.1, R255.2, U113.1
T7/KA_CUT: R59.1, U20.6, U112.6
T7/PHY1/sel_sw: R262.2, U114.4, U115.6
T7/PHY1/txa_sw: R258.1, U115.4
T7/POT_PWM: R255.1, U28.28
T7/POT_SEL: R5.1, U10.3, U113.6
T7/PWR: Q16.1, R256.1, U20.7
T7/RX_B#a: R259.1, U109.4
T7/SHG_A: R60.1, U20.1, U107.6
T7/SHG_B: R61.1, U20.4, U110.6
T7/SHV_A: R62.1, U20.2, U108.6
T7/SHV_B: R63.1, U20.5, U111.6
T7/SL1/led_x: LED29.1, LED31.2, R271.2
T7/SL1/ledw_a: LED32.2, R272.2
T7/SL1/pwr_led: LED30.2, R270.2
T7/TX_A#a: R258.2, U106.4
T7/WD1/kap: C68.1, R274.2
T7/WD1/x: C68.2, D12.3
T7/btn_a: Q14.3, R265.1, R267.1, SW7.1
T7/btn_b: Q15.3, R266.1, R268.1, SW8.1
T7/button_a: R267.2, U116.15
T7/button_b: R268.2, U116.16
T7/debug_tx: U7.1, U116.2
T7/ka#a: U112.4, U116.20
T7/ka#b: R254.1, R274.1, U112.3
T7/led_seg: R271.1, U116.10
T7/led_work: R272.1, U116.8
T7/opa_n: R263.2, R264.1, U116.5
T7/opa_p: R257.2, R261.2, U115.3, U116.6
T7/opa_p_b: R259.2, U116.4
T7/opo: R261.1, U116.1
T7/pc7: TP32.1, U116.17
T7/pot: R269.2, U116.3
T7/pot_w#a: RV4.2, U113.3
T7/pot_w#b: R269.1, U113.4
T7/sel: C69.1, D12.2, R262.1, R273.1, U12.5, U114.2, U116.12
T7/swio: R87.1, TP29.1, U36.1, U116.18
T7/txa_drv: U115.1, U116.19
T7/txb_drv: R260.1, U116.13
UNREG: J1.1, J3.1
USB_DM: J2.A7, J2.B7, R75.1
USB_DP: J2.A6, J2.B6, R74.1
commit: U8.12, U9.12, U10.12, U11.1, U12.1, U13.12, U14.12, U15.12, U16.12, U17.12, U18.12, U19.12, U20.12, U28.32
dbg_rx: U1.4, U28.16
oe_n: R1.1, U8.13, U9.13, U10.13, U13.13, U14.13, U15.13, U16.13, U17.13, U18.13, U19.13, U20.13, U28.34
sdi: U12.9, U28.31
sdo: U8.14, U28.30
srclk: U8.11, U9.11, U10.11, U11.2, U12.2, U13.11, U14.11, U15.11, U16.11, U17.11, U18.11, U19.11, U20.11, U28.29
swio: R88.1, U28.15, U30.4
swio_a0: R12.1, U4.6, U5.6, U6.6, U7.6, U8.6, U33.6, U34.6, U35.6, U36.6
swio_a1: R13.1, U2.6, U3.6, U8.7, U31.6, U32.6
swio_a2: R14.1, U1.6, U9.15, U30.6

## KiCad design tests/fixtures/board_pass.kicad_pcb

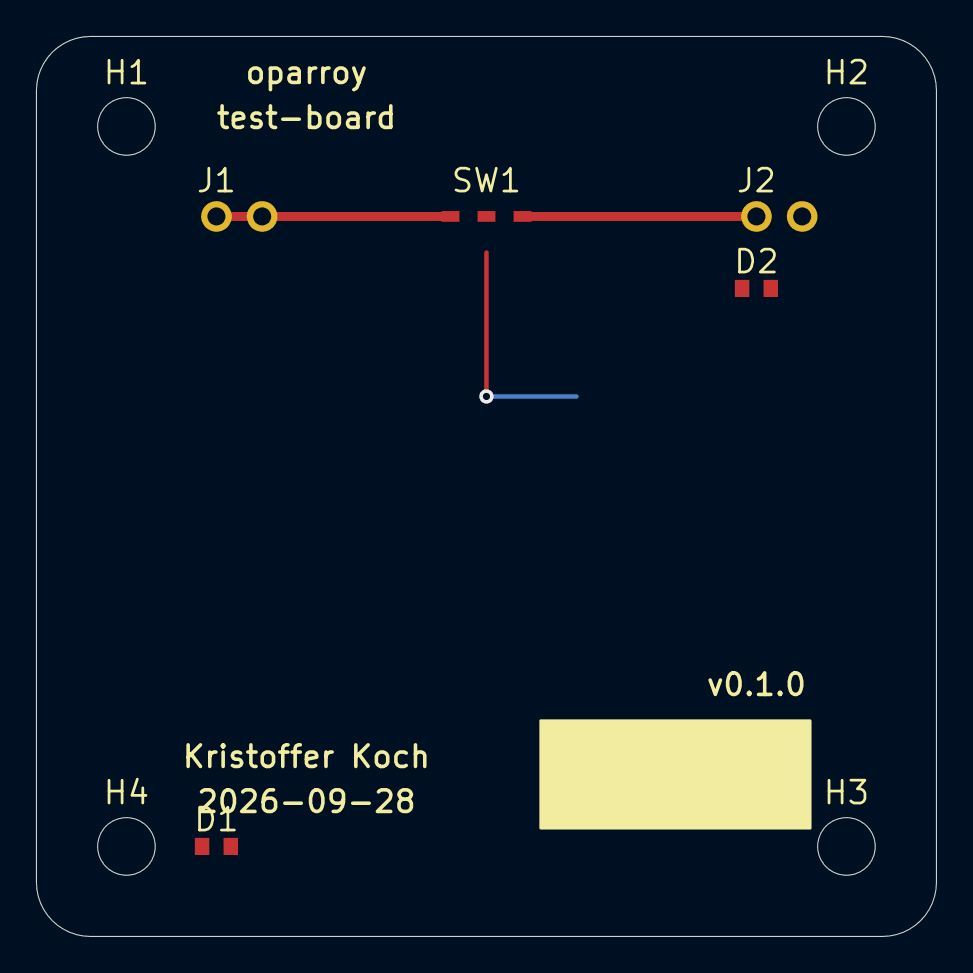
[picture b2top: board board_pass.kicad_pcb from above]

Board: 2 copper layers, 50.0 x 50.0 mm, 9 parts (0 on the bottom side), 3 nets.

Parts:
D1, D2: LED; LED_0603
H1, H2, H3, H4: MountingHole; MountingHole_3.2mm_M3
J1, J2: CONN6; CONN_1x06
SW1: SN74LVC1G3157; SPDT

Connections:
BYPASS: J1.1, J2.1, SW1.1, SW1.2
GND: D1.1, D2.1, J1.2, J2.2
SIG: D1.2, D2.2, SW1.3

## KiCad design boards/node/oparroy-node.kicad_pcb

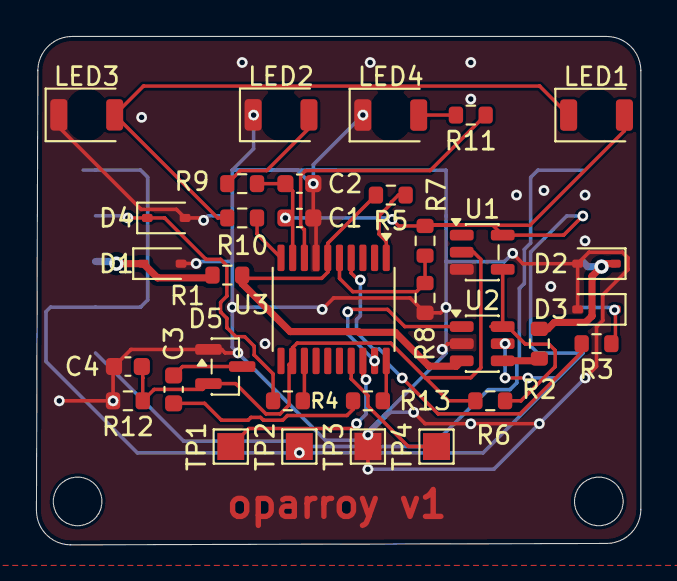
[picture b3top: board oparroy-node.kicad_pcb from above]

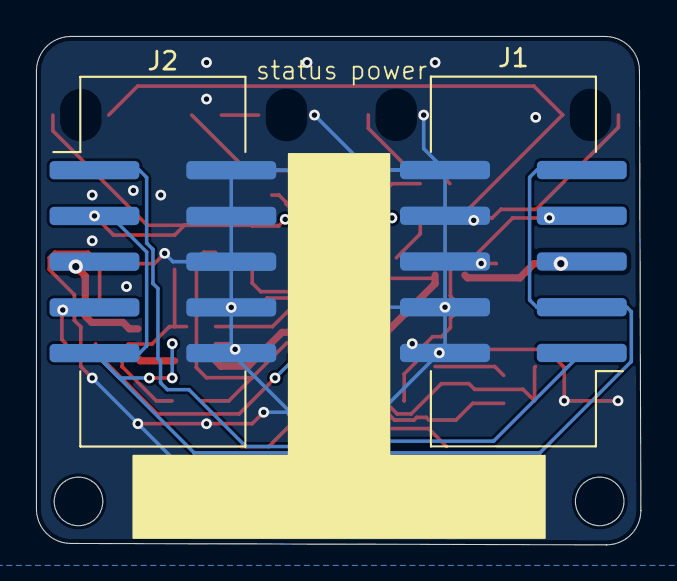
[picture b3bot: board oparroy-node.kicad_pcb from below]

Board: 2 copper layers, 33.6 x 28.2 mm, 35 parts (2 on the bottom side), 26 nets.

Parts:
C1: 100n; C_0603_1608Metric
C2: 10u; C_0603_1608Metric
C3: 22n; C_0603_1608Metric
C4: 10n; C_0603_1608Metric
D1, D2, D3, D4: UDD32C03L01; D_SOD-323
D5: BAT54S; SOT-23
J1, J2: Conn_02x05_Odd_Even; IDC-Header_2x05_P2.54mm_Vertical_SMD
LED1, LED3: XL-3216SYGC-FB; LED_1206_3216Metric_ReverseMount_Hole1.5x2.4mm
LED2: XL-3216SURC-FB; LED_1206_3216Metric_ReverseMount_Hole1.5x2.4mm
LED4: XL-3216UYC-FB; LED_1206_3216Metric_ReverseMount_Hole1.5x2.4mm
R1, R2, R3, R4, R10: 470; R_0603_1608Metric
R5: DNP; R_0603_1608Metric
R6: 0R; R_0603_1608Metric
R7, R8: 10k; R_0603_1608Metric
R9, R11: 1k; R_0603_1608Metric
R12: 47k; R_0603_1608Metric
R13: 220; R_0603_1608Metric
TP1: SWIO; TestPoint_Pad_1.5x1.5mm
TP2: 3V3; TestPoint_Pad_1.5x1.5mm
TP3: GND; TestPoint_Pad_1.5x1.5mm
TP4: PC7; TestPoint_Pad_1.5x1.5mm
U1: DNP; SOT-23-5
U2: SN74LVC1G3157; SOT-23-6
U3: CH32V003F4P6; TSSOP-20_4.4x6.5mm_P0.65mm

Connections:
3V3: C1.1, C2.1, J1.3, J1.9, J2.3, J2.9, LED1.2, R7.1, R9.1, TP2.1, U1.5, U2.5, U3.9
GND: C1.2, C2.2, C4.2, D1.2, D2.2, D3.2, D4.2, D5.1, J1.2, J1.4, J1.6, J1.8, J1.10, J2.2, J2.4, J2.6, J2.8, J2.10, LED2.1, LED3.1, LED4.1, R8.2, R12.2, TP3.1, U1.3, U2.2, U3.7
PHY1/sel_sw: R6.2, U1.4, U2.6
PHY1/txa_sw: R2.1, U2.4
RX_A: D1.1, J1.5, R1.1
RX_B: D3.1, J2.7, R3.1
SL1/led_x: LED1.1, LED3.2, R10.2
SL1/ledw_a: LED4.2, R11.2
SL1/pwr_led: LED2.2, R9.2
TX_A: D2.1, J2.5, R2.2
TX_B: D4.1, J1.7, R4.2
UNREG: J1.1, J2.1
WD1/kap: C3.1, R13.2
WD1/x: C3.2, D5.3
ka: R13.1, U3.20
led_seg: R10.1, U3.10
led_work: R11.1, U3.8
opa_n: R7.2, R8.1, U3.5
opa_p: R1.2, R5.2, U2.3, U3.6
opa_p_b: R3.2, U3.4
opo: R5.1, U3.1
pc7: TP4.1, U3.17
sel: C4.1, D5.2, R6.1, R12.1, U1.2, U3.12
swio: TP1.1, U3.18
txa_drv: U2.1, U3.19
txb_drv: R4.1, U3.13
